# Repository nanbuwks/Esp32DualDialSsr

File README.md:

# Esp32DualDialSsr

ESP32 board with 2 rotary encoder and 4 ch SSR.

# OVERVIEW

include AC to 12V DC power module and AC (SSR driven 12V). 

# User Interface
2 rotary encoder and 3.2in TFT LCD module connector

# OUTPUT

2 output but 1ch 12V ON/OFF output for 12V FAN. 

3 + 1 SSR output

Power IN connector (J2) , fuse (F1) and one of SSR output (J5) 

buzzer and temp sensor(optional)

# GPIO settings

## TFT LCD

```
  static constexpr int dma_channel = 1;
  static constexpr int spi_sclk = 18;
  static constexpr int spi_mosi = 23;
  static constexpr int spi_miso = 19;
  static constexpr int spi_dlen = 8;
#define TFT_RST 16
#define TFT_DC 17
#define TFT_CS 5
#define TFT_BACKLIGHT_PIN 4
```

## Rotary Encoder

#define ENCODER1_A_PIN 34
#define ENCODER1_B_PIN 35
#define ENCODER1_SWITCH_PIN 25
#define ENCODER2_A_PIN 12
#define ENCODER2_B_PIN 13
#define ENCODER2_SWITCH_PIN 14

## SSR

```
#define PUMP_PIN 27
SSR control GPIO 26,32,33
```

# OTHER

```
#define FAN_PIN 22
#define BEEP_PIN 2
```

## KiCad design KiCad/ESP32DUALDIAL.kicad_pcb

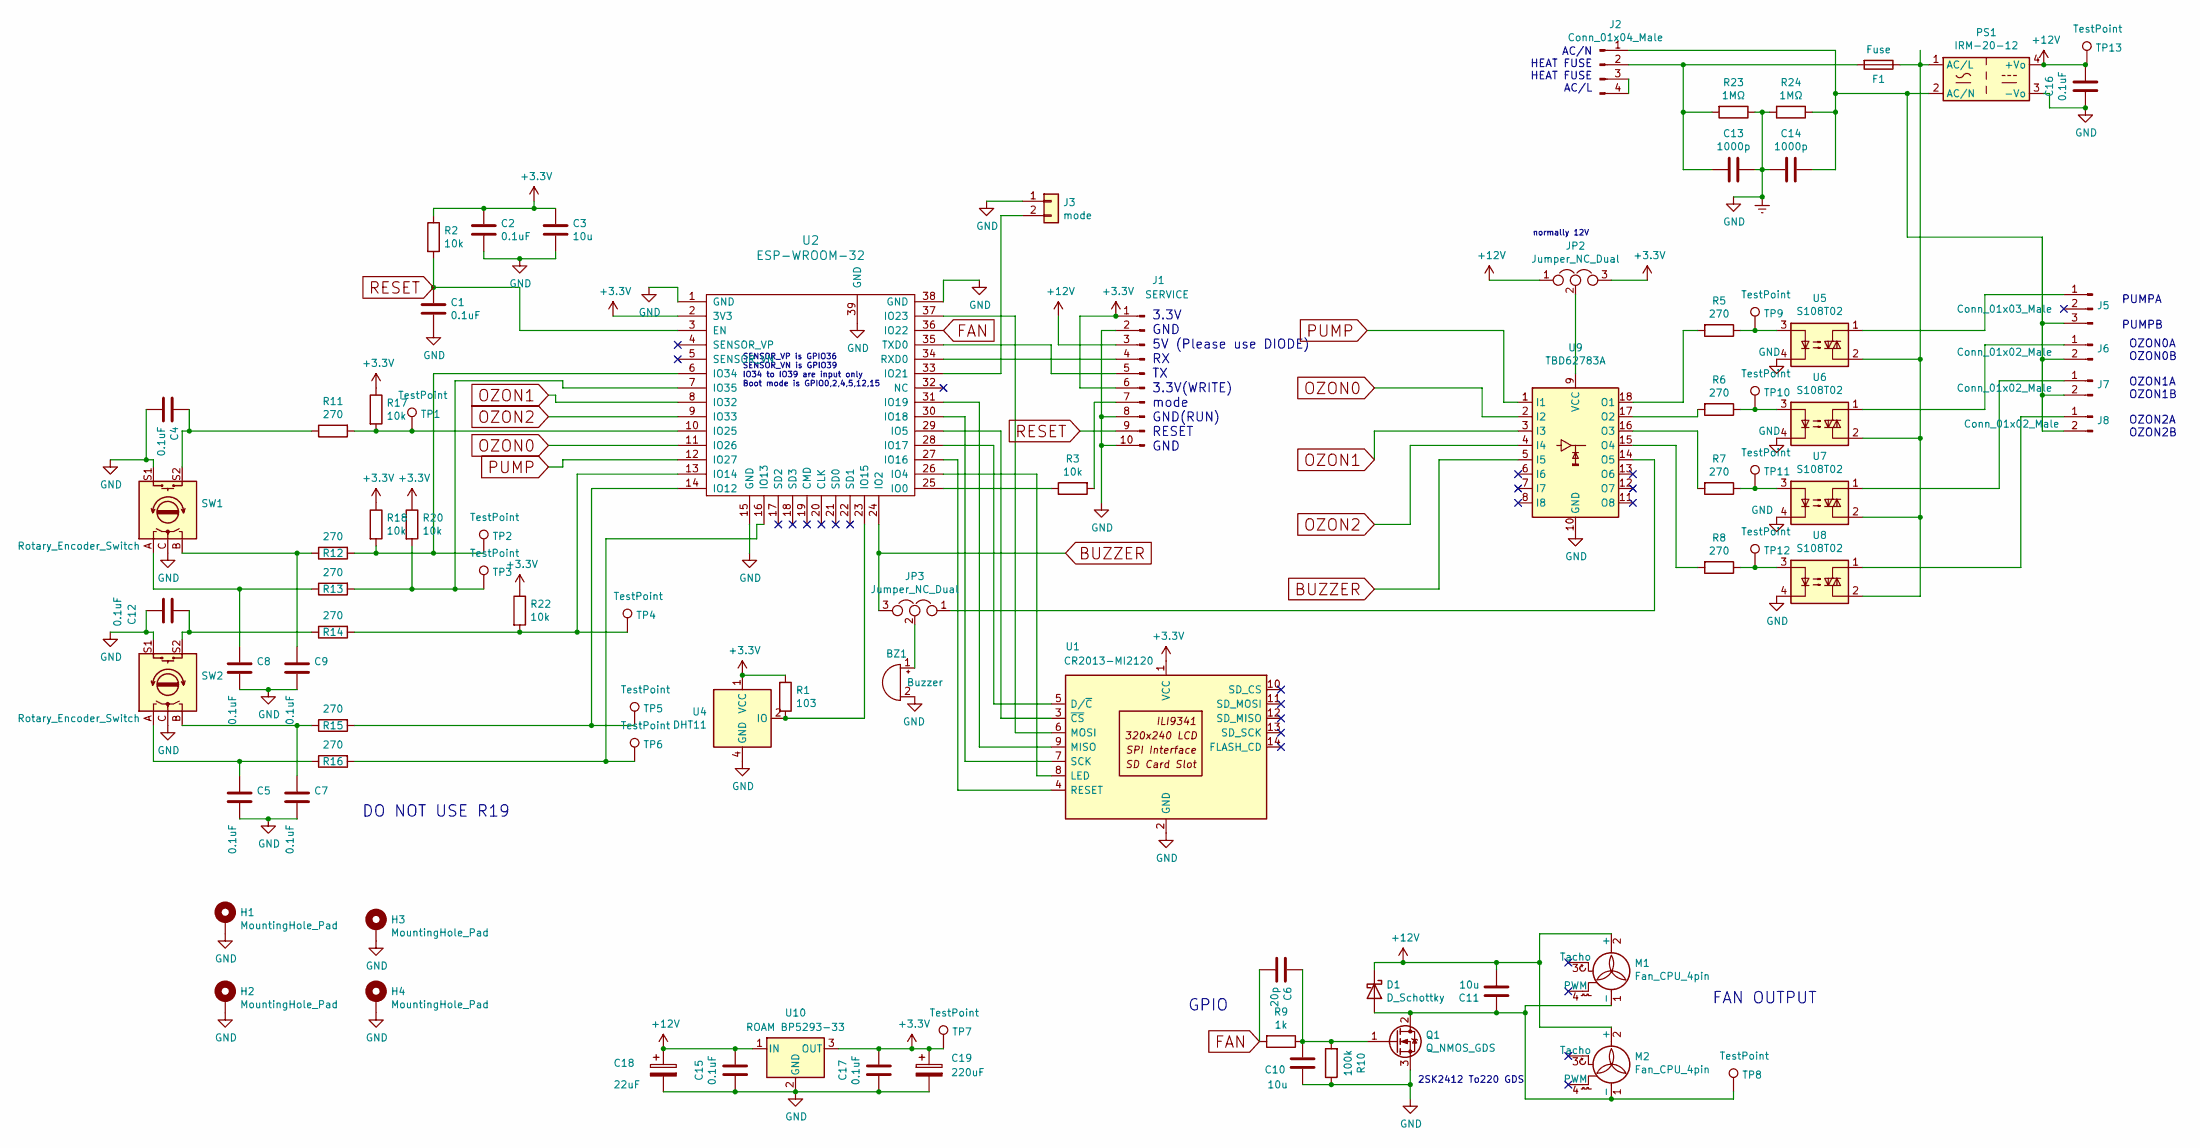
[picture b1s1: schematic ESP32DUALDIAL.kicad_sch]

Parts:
BZ1: Buzzer; Buzzer_7.6_5.0
C1, C2, C4, C5, C7, C8, C9, C12: 0.1uF; R_0603_1608Metric
C3, C10, C11: 10u; C_0402_1005Metric
C6: 20p; C_0402_1005Metric
C13, C14: 1000p; C_Disc_D10.5mm_W5.0mm_P10.00mm
C15, C16, C17: 0.1uF; C_0603_1608Metric
C18: 22uF; CP_Radial_D6.3mm_P2.50mm
C19: 220uF; CP_Radial_D5.0mm_P2.00mm
D1: D_Schottky; D_SOD-123F
F1: Fuse; 20mmFuse_P5x2
H1, H2, H3, H4: MountingHole_Pad; MountingHole_3.2mm_M3_Pad
J1: SERVICE; PinHeader_1x10_P2.54mm_Vertical
J2: Conn_01x04_Male; JST_NV_B04P-NV_1x04_P5.00mm_Vertical
J3: mode; PinHeader_2x01_P2.54mm_Vertical
J5: Conn_01x03_Male; JST_VH_B3P-VH_1x03_P3.96mm_Vertical
J6, J7, J8: Conn_01x02_Male; JST_NV_B02P-NV_1x02_P5.00mm_Vertical
JP2, JP3: Jumper_NC_Dual; SolderJumper-3_P1.3mm_Bridged12_RoundedPad1.0x1.5mm_NumberL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
M1, M2: Fan_CPU_4pin; FanPinHeader_1x03_P2.54mm_Vertical
PS1: IRM-20-12; Converter_ACDC_MeanWell_IRM-20-xx_THT
Q1: Q_NMOS_GDS; TO-252-2
R1: 103; R_0603_1608Metric
R2, R3, R17, R18, R20, R22: 10k; R_0603_1608Metric
R5, R6, R7, R8, R11, R12, R13, R14, R15, R16: 270; R_0603_1608Metric
R9: 1k; R_0603_1608Metric
R10: 100k; R_0603_1608Metric
R23, R24: 1MΩ; R_Axial_DIN0207_L6.3mm_D2.5mm_P10.16mm_Horizontal
SW1, SW2: Rotary_Encoder_Switch; RotaryEncoder_Alps_EC11E-Switch_Vertical_H20mm
TP1, TP2, TP3, TP4, TP5, TP6, TP8, TP9, TP10, TP11, TP12: TestPoint; TestPoint_Pad_D2.0mm
TP7, TP13: TestPoint; TestPoint_Pad_D3.0mm
U1: CR2013-MI2120; TFT3.2_ILI9341
U2: ESP-WROOM-32
U4: DHT11; Aosong_DHT11_5.5x12.0_P2.54mm
U5, U6, U7, U8: S108T02; SSR_SHARP_S108T02_NNC_NNG1D-25mm
U9: TBD62783A; SOIC-18W_7.5x11.6mm_P1.27mm
U10: ROAM BP5293-33; Converter_DCDC_RECOM_R-78E-0.5_THT

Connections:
+3V3: C2.1, C3.1, C17.1, C19.1, J1.1, J1.6, JP2.3, R1.1, R2.1, R17.1, R18.1, R20.1, R22.1, TP7.1, U1.1 (VCC), U2.2 (3V3), U4.1 (VCC), U10.3 (OUT)
+12V: C11.2, C15.1, C16.1, C18.1, D1.1 (K), J1.3, JP2.1, M1.2 (+), M2.2 (+), PS1.4 (+Vo), TP13.1, U10.1 (IN)
BUZZER: JP3.3, U2.24 (IO2), U9.5 (I5)
Earth: BZ1.2 (+), C1.2, C2.2, C3.2, C4.2, C5.2, C7.2, C8.2, C9.2, C10.1, C12.2, C13.1, C14.2, C15.2, C16.2, C17.2, C18.2, C19.2, H1.1, H2.1, H3.1, H4.1, J1.2, J1.8, J1.10, J3.1, PS1.3 (-Vo), Q1.3 (S), R10.1, R23.1, R24.2, SW1.C, SW1.S1, SW2.C, SW2.S1, U1.2 (GND), U2.1 (GND), U2.15 (GND), U2.38 (GND), U2.39 (GND), U4.4 (GND), U5.4, U6.4, U7.4, U8.4, U9.10 (GND), U10.2 (GND)
FAN: C6.2, R9.2, U2.36 (IO22)
unnamed: BZ1.1 (-), JP3.2
unnamed: C4.1, R11.1, SW1.S2
unnamed: C5.1, R16.1, SW2.A
unnamed: C7.1, R15.1, SW2.B
unnamed: C8.1, R13.1, SW1.A
unnamed: C9.1, R12.1, SW1.B
unnamed: C12.1, R14.1, SW2.S2
unnamed: C11.1, D1.2 (A), M1.1 (-), M2.1 (-), Q1.2 (D), TP8.1
unnamed: J1.4, U2.34 (RXD0)
unnamed: J1.5, U2.35 (TXD0)
unnamed: J1.7, R3.2
unnamed: C14.1, J2.1, J5.3, J6.2, J7.2, J8.2, PS1.2 (AC/N), R24.1
unnamed: C13.2, F1.2, J2.2, R23.2
unnamed: J2.3, J2.4
unnamed: J3.2, U2.33 (IO21)
unnamed: J5.1, U5.1
unnamed: J6.1, U6.1
unnamed: J7.1, U7.1
unnamed: J8.1, U8.1
unnamed: F1.1, PS1.1 (AC/L), U5.2, U6.2, U7.2, U8.2
unnamed: C6.1, C10.2, Q1.1 (G), R9.1, R10.2
unnamed: R5.1, TP9.1, U5.3
unnamed: R6.1, TP10.1, U6.3
unnamed: R7.1, TP11.1, U7.3
unnamed: R8.1, TP12.1, U8.3
unnamed: U1.5 (D/~C), U2.28 (IO17)
unnamed: U1.8 (LED), U2.26 (IO4)
unnamed: U1.9 (MISO), U2.31 (IO19)
unnamed: U1.6 (MOSI), U2.37 (IO23)
unnamed: U1.4 (RESET), U2.27 (IO16)
unnamed: U1.7 (SCK), U2.30 (IO18)
unnamed: U1.3 (~CS), U2.29 (IO5)
unnamed: R3.1, U2.25 (IO0)
unnamed: R15.2, TP5.1, U2.14 (IO12)
unnamed: R16.2, TP6.1, U2.16 (IO13)
unnamed: R14.2, R22.2, TP4.1, U2.13 (IO14)
unnamed: R1.2, U2.23 (IO15), U4.2 (IO)
unnamed: R11.2, R17.2, TP1.1, U2.10 (IO25)
unnamed: R12.2, R18.2, TP2.1, U2.6 (IO34)
unnamed: R13.2, R20.2, TP3.1, U2.7 (IO35)
unnamed: R5.2, U9.18 (O1)
unnamed: R6.2, U9.17 (O2)
unnamed: R7.2, U9.16 (O3)
unnamed: R8.2, U9.15 (O4)
unnamed: JP3.1, U9.14 (O5)
unnamed: JP2.2, U9.9 (VCC)
OZON0: U2.11 (IO26), U9.2 (I2)
OZON1: U2.8 (IO32), U9.3 (I3)
OZON2: U2.9 (IO33), U9.4 (I4)
PUMP: U2.12 (IO27), U9.1 (I1)
RESET: C1.1, J1.9, R2.2, U2.3 (EN)

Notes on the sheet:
normally 12V
FAN OUTPUT
3.3V GND 5V (Please use DIODE) RX TX 3.3V(WRITE) mode GND(RUN) RESET GND
OZON0A OZON0B OZON1A OZON1B OZON2A OZON2B
GPIO
AC/N HEAT FUSE HEAT FUSE AC/L
PUMPA PUMPB
2SK2412 To220 GDS
DO NOT USE R19
SENSOR_VP is GPIO36 SENSOR_VN is GPIO39 IO34 to IO39 are input only Boot mode is GPIO0,2,4,5,12,15

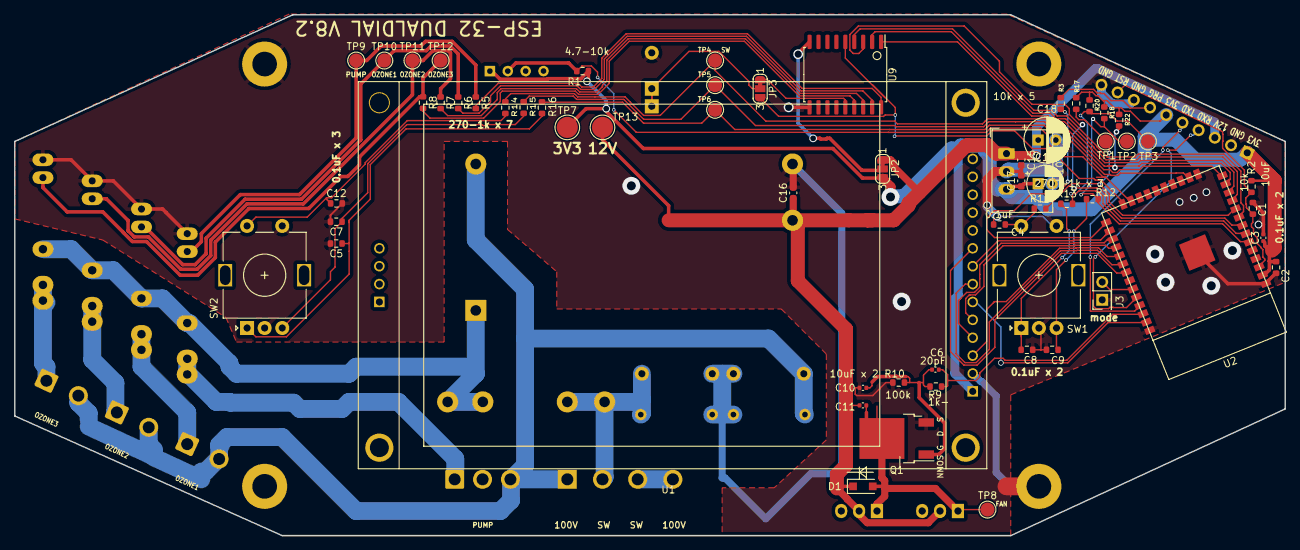
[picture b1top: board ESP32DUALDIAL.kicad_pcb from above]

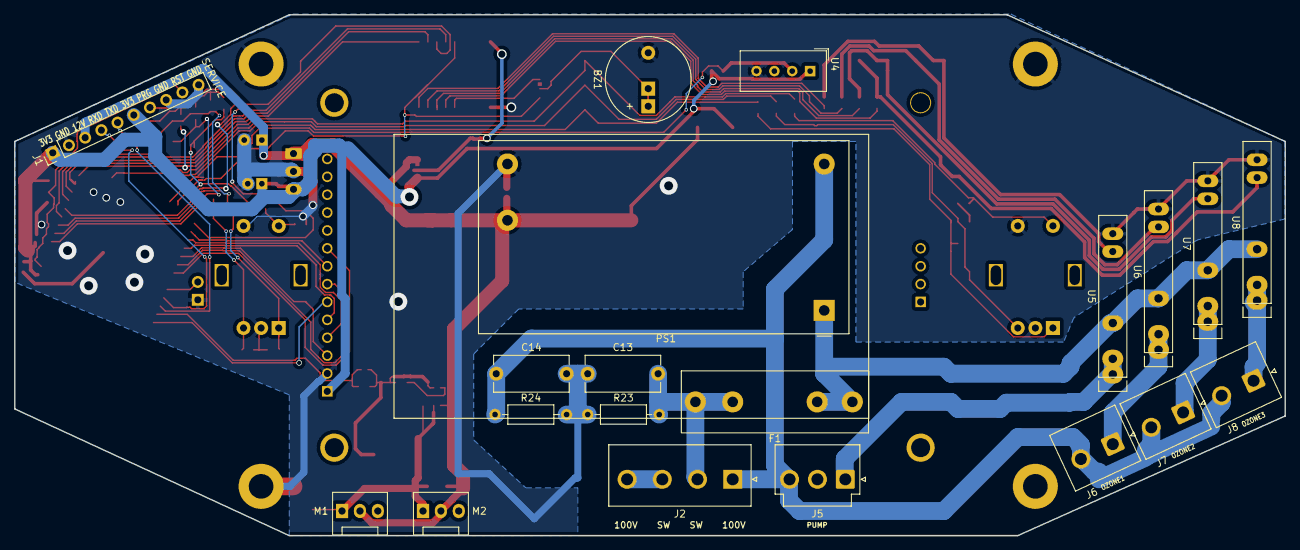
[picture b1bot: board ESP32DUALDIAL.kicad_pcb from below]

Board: 2 copper layers, 180.5 x 74.0 mm, 84 parts (20 on the bottom side), 56 nets.

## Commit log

2021-01-16 change SSR SHARP S108T02
2021-01-27 version 20210119
2021-01-31 fix GPIO assign bug.
2021-03-10 change to ROTARY ENCODER chattaling fix. and many change...
2021-07-23 Ver.6 : Add test pads / NNC and SHARP SSR both support / mode jumper
2021-10-26 Version6 release. Testpad add and follow more SSR type.
2021-11-16 add firmware directory
2021-11-16 fix eeprom first use check
2021-11-16 change to version 1.1 / EEPROM param int 4 byte x 13 from 4 byte x 10
2021-11-16 add stopFUN()
2021-11-16 move caution txt from main program to commercial.h
2021-11-16 bug fix eeprom paramater 10 to 12
2021-11-16 OZONE pin change to array from DEFINE
2023-04-15 modify Arduino sketch
2023-04-15 README clear
2023-04-15 change README
2023-08-22 arduino schtch update
2023-10-12 V8 release
2023-10-13 change to V8.1
2023-11-10 firmware update to 1.3
2023-11-10 firmware update to 1.4
2023-12-01 change sketch 1.41w
2025-07-16 change to V8.2
